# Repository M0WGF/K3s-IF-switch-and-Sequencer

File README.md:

# K3/s IF switch and Sequencer
Two port IF switch and three event sequencer for use with the Elecraft K3 and K3s transceivers. 

Switch between two external transverters directly from the Elecraft K3/s transceiver, the unit also comes with a three
port sequencer where the first event is for switching a relay and the last two events pull to ground.

The unit is based around an Arduino UNO see the .ino file for the script, it uses one no standard library which is
called Bounce2 and be downloaded from https://github.com/thomasfredericks/Bounce2

The unit has also been designed so that when the VSWR trip is pulled to ground the unit goes into a disabled state
stopping the transmitter and sounding a buzzer until the unit is reset. 

There are two boards the main board and an indicator board.  

The software has few parameters that can be changed look towards the top of the .ino file these are

// Event Sequence Delays 

int Sequence_Delay = 50; // Delay in milliseconds.
int Txinhibit_Delay = 50; 

// Default RX behaviour of events HIGH = On; LOW = Off.   Event 1 is capable of providing upto 28V 1A, and by default is 
set to energise the relay for RX.

int band0_event1 = HIGH;
int band0_event2 = LOW;
int band0_event3 = LOW;

int band1_event1 = HIGH;
int band1_event2 = LOW;
int band1_event3 = LOW;

// Debugging will output the debugs to the serial port. 
bool debug_main = false;

For further details see : 
https://m0wgf.blogspot.com/2019/12/dual-transverter-if-switch-and.html

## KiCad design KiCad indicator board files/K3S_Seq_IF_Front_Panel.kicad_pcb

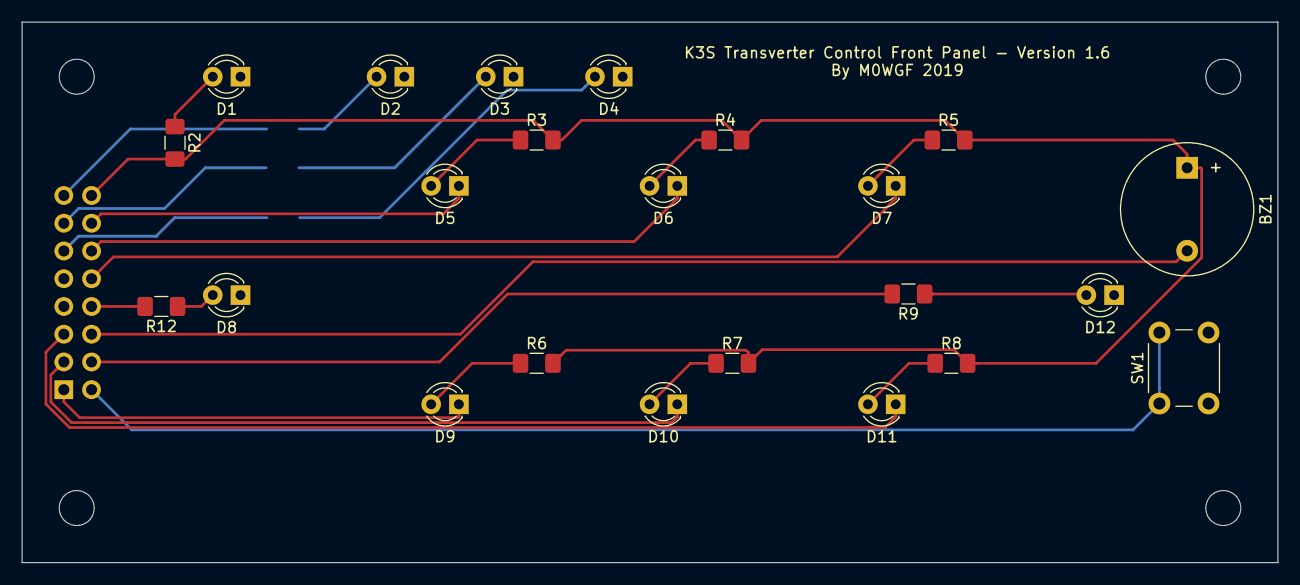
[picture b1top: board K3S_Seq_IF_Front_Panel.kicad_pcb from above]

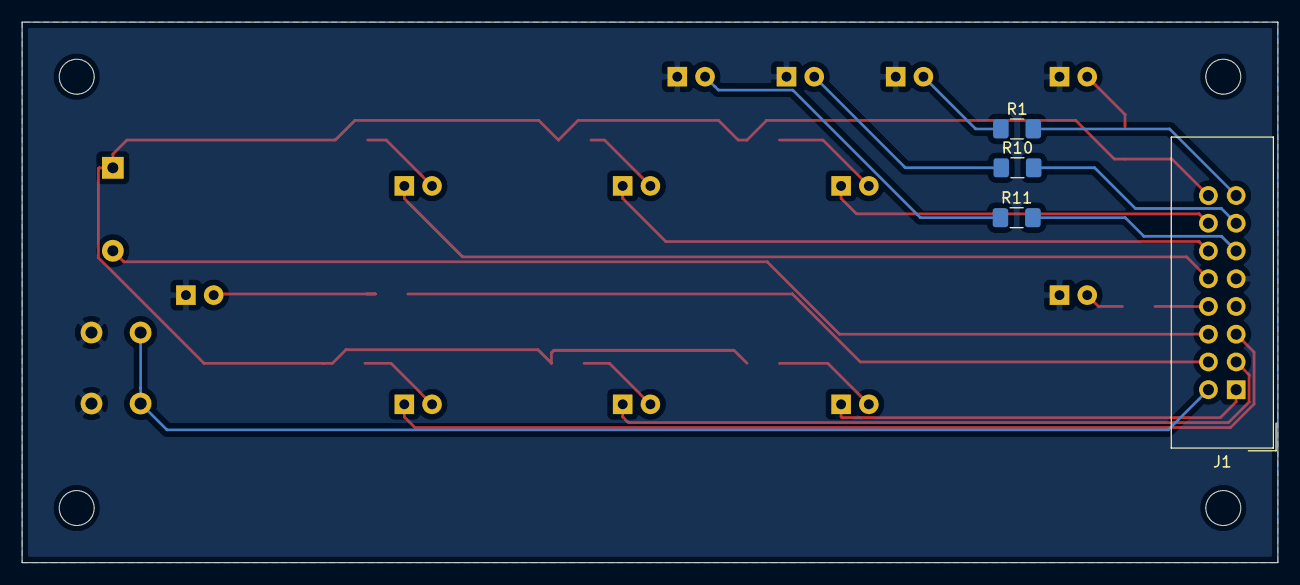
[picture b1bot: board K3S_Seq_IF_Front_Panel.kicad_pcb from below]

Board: 2 copper layers, 115.0 x 49.5 mm, 27 parts (4 on the bottom side), 27 nets.

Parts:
BZ1: VSWR Trip Buzzer; Buzzer_12x9.5RM7.6
D1: Power; LED_D3.0mm
D2: Band 0; LED_D3.0mm
D3: Band 1; LED_D3.0mm
D4: Band 2; LED_D3.0mm
D5: Band 0 Event 1; LED_D3.0mm
D6: Band 0 Event 2; LED_D3.0mm
D7: Band 0 Event 3; LED_D3.0mm
D8: PTT; LED_D3.0mm
D9: Band 1 Event 1; LED_D3.0mm
D10: Band 1 Event 2; LED_D3.0mm
D11: Band 1 Event 3; LED_D3.0mm
D12: Tx Inhibit; LED_D3.0mm
J1: Conn_02x08_Odd_Even; IDC-Header_2x08_P2.54mm_Vertical
R1, R2, R3, R4, R5, R6, R7, R8, R9, R10, R11, R12: 360; R_1206_3216Metric_Pad1.42x1.75mm_HandSolder
SW1: RESET SW; SW_PUSH_6mm

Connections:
+5V: BZ1.1, J1.16, R2.2, R3.2, R4.2, R5.2, R6.2, R7.2, R8.2
Band0_Event1_Led: D5.1, J1.14
Band0_Event2_Led: D6.1, J1.12
Band0_Event3_Led: D7.1, J1.10
Band0_Led: J1.15, R1.2
Band1_Event1_Led: D9.1, J1.1
Band1_Event2_Led: D10.1, J1.3
Band1_Event3_Led: D11.1, J1.5
Band1_Led: J1.13, R10.2
Band2_Led: J1.11, R11.2
Buzzer: BZ1.2, J1.6
GND: D1.1, D2.1, D3.1, D4.1, D8.1, D12.1, J1.9, SW1.2
unnamed: D1.2, R2.1
unnamed: D2.2, R1.1
unnamed: D3.2, R10.1
unnamed: D4.2, R11.1
unnamed: D5.2, R3.1
unnamed: D6.2, R4.1
unnamed: D7.2, R5.1
unnamed: D8.2, R12.1
unnamed: D9.2, R6.1
unnamed: D10.2, R7.1
unnamed: D11.2, R8.1
unnamed: D12.2, R9.1
PTT_Led: J1.8, R12.2
Reset: J1.2, SW1.1
TxInhibit_Led: J1.4, R9.2

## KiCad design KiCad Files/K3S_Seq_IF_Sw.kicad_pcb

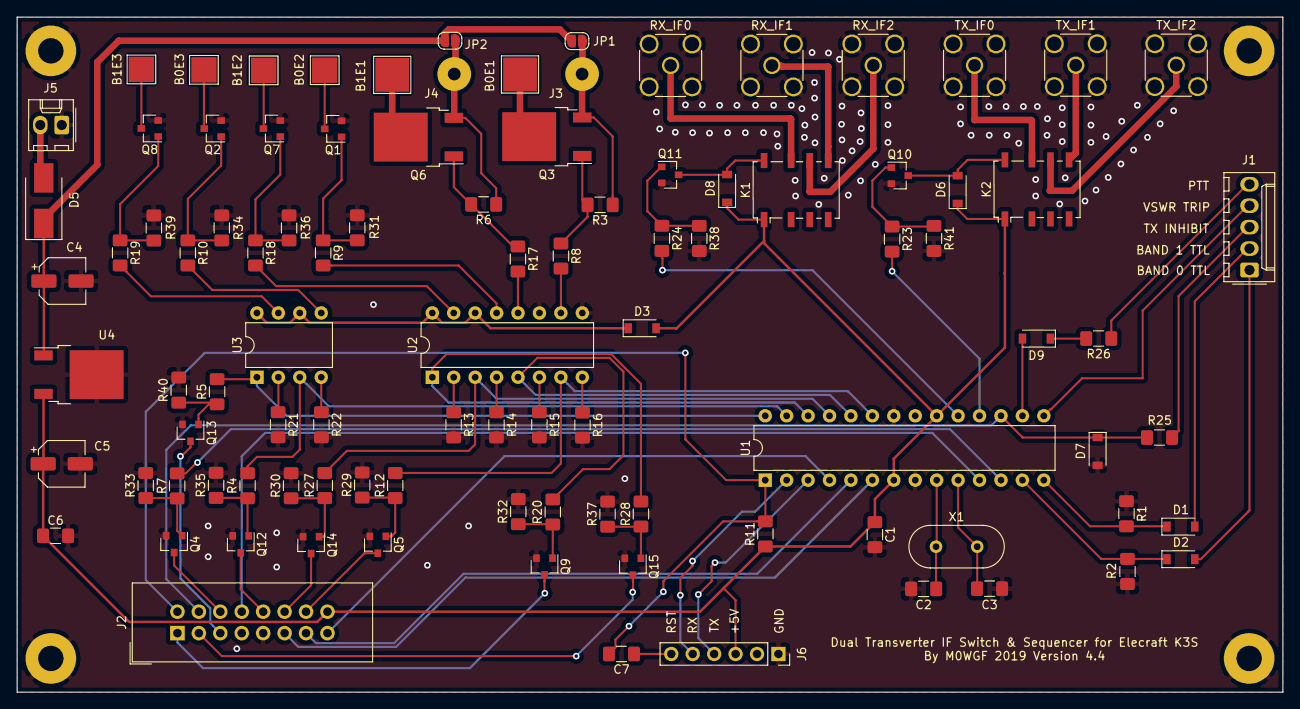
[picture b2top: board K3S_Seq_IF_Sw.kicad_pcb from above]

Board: 2 copper layers, 150.0 x 80.0 mm, 102 parts (0 on the bottom side), 84 nets.

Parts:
B0E1, B1E1: Conn_01x01; TestPoint_Pad_4.0x4.0mm
B0E2, B0E3, B1E2, B1E3: Conn_01x01; TestPoint_Pad_3.0x3.0mm
C1, C6, C7: 100nF; C_1206_3216Metric_Pad1.42x1.75mm_HandSolder
C2, C3: 22pF; C_1206_3216Metric_Pad1.42x1.75mm_HandSolder
C4, C5: 47uF; CP_Elec_5x5.8
D1, D2, D3, D6, D8, D9: D; D_SOD-123
D5: D; D_SMB_Handsoldering
D7: 5V1; D_SOD-123
H1, H2, H3, H4: MountingHole; MountingHole_3mm_Pad
J1: K3S & Wavenode; Molex_KK-254_AE-6410-05A_1x05_P2.54mm_Vertical
J2: Indicator Panel; IDC-Header_2x08_P2.54mm_Vertical
J3, J4: 12V; SolderWirePad_1x01_Drill1.5mm
J5: PWR; Molex_KK-254_AE-6410-02A_1x02_P2.54mm_Vertical
J6: Programming Interface; PinSocket_1x06_P2.54mm_Vertical
JP1, JP2: Jumper; SolderJumper-2_P1.3mm_Open_RoundedPad1.0x1.5mm
K1, K2: G6K-2; Relay_DPDT_Omron_G6K-2F-Y
Q1, Q2, Q4, Q5, Q7, Q8, Q9, Q10, Q11, Q12, Q13, Q14, Q15: MMBT3904; SOT-23
Q3, Q6: DMP4015SK3; TO-252-2
R1, R2, R3, R6, R11, R25, R26, R29, R30, R31, R32, R33, R34, R35, R36, R37, R38, R39, R40, R41: 10k; R_1206_3216Metric_Pad1.42x1.75mm_HandSolder
R4, R5, R7, R9, R10, R12, R18, R19, R20, R23, R24, R27, R28: 2k2; R_1206_3216Metric_Pad1.42x1.75mm_HandSolder
R8, R17: 100; R_1206_3216Metric_Pad1.42x1.75mm_HandSolder
R13, R14, R15, R16, R21, R22: 330; R_1206_3216Metric_Pad1.42x1.75mm_HandSolder
RX_IF0: RX_IF0; SMA_Amphenol_132134-16_Vertical
RX_IF1: RX_IF1; SMA_Amphenol_132134-16_Vertical
RX_IF2: RX_IF; SMA_Amphenol_132134-16_Vertical
TX_IF0: TX_IF0; SMA_Amphenol_132134-16_Vertical
TX_IF1: TX_IF1; SMA_Amphenol_132134-16_Vertical
TX_IF2: TX_IF; SMA_Amphenol_132134-16_Vertical
U1: ATmega328P-PU; DIP-28_W7.62mm
U2: LTV-847S; DIP-16_W7.62mm
U3: LTV-827S; DIP-8_W7.62mm
U4: MC7805BDTG; TO-252-2
X1: Crystal; Crystal_HC49-U_Vertical

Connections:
+5V: C1.1, C5.1, C6.1, D3.2, D6.1, D8.1, J2.16, J6.3, K1.1, K2.1, R11.1, U1.7, U1.20, U4.3
+12V: C4.1, D5.1, JP1.1, JP2.1, U4.1
Band0_Event1: R12.2, U1.23, U2.7
Band0_Event1_Led: J2.14, Q5.3
Band0_Event2: R27.2, U1.25, U2.3
Band0_Event2_Led: J2.12, Q14.3
Band0_Event3: R4.2, U1.27, U3.3
Band0_Event3_Led: J2.10, Q12.3
Band0_Input: D2.2, J1.1
Band0_Led: J2.15, U1.4
Band1_Event1: R20.2, U1.24, U2.5
Band1_Event1_Led: J2.1, Q9.3
Band1_Event2: R28.2, U1.26, U2.1
Band1_Event2_Led: J2.3, Q15.3
Band1_Event3: R5.2, U1.28, U3.1
Band1_Event3_Led: J2.5, Q13.3
Band1_Input: D1.2, J1.2
Band1_Led: J2.13, U1.5
Band2_Led: J2.11, U1.6
Buzzer: J2.6, Q4.3
D0: J6.5, U1.2
D1: J6.4, U1.3
GND: C1.2, C2.2, C3.2, C4.2, C5.2, C6.2, D7.2, H1.1, H2.1, H3.1, H4.1, J2.9, J5.1, J6.1, Q1.2, Q2.2, Q4.2, Q5.2, Q7.2, Q8.2, Q9.2, Q10.2, Q11.2, Q12.2, Q13.2, Q14.2, Q15.2, R1.1, R2.2, R13.2, R14.2, R15.2, R16.2, R21.2, R22.2, R29.2, R30.2, R31.2, R32.2, R33.2, R34.2, R35.2, R36.2, R37.2, R38.2, R39.2, R40.2, R41.2, RX_IF0.2, RX_IF1.2, RX_IF2.2, TX_IF0.2, TX_IF1.2, TX_IF2.2, U1.8, U1.22, U2.9, U2.11, U4.2
IF_RX: R24.2, U1.19
IF_TX: R23.2, U1.18
unnamed: B0E1.1, Q3.2
unnamed: B0E2.1, Q1.3
unnamed: B0E3.1, Q2.3
unnamed: B1E1.1, Q6.2
unnamed: B1E2.1, Q7.3
unnamed: B1E3.1, Q8.3
unnamed: C2.1, U1.9, X1.1
unnamed: C3.1, U1.10, X1.2
unnamed: C7.1, J6.6
unnamed: D1.1, R1.2, U1.14
unnamed: D2.1, R2.1, U1.13
unnamed: D5.2, J5.2
unnamed: D6.2, K2.8, Q10.3
unnamed: D8.2, K1.8, Q11.3
unnamed: D9.1, R26.2
unnamed: D9.2, U1.16
unnamed: J3.1, JP1.2, Q3.3, R3.1
unnamed: J4.1, JP2.2, Q6.3, R6.1
unnamed: K1.5, RX_IF1.1
unnamed: K1.6, RX_IF2.1
unnamed: K1.7, RX_IF0.1
unnamed: K2.5, TX_IF1.1
unnamed: K2.6, TX_IF2.1
unnamed: K2.7, TX_IF0.1
unnamed: Q1.1, R9.1, R31.1
unnamed: Q2.1, R10.1, R34.1
unnamed: Q3.1, R3.2, R8.1
unnamed: Q4.1, R7.1, R33.1
unnamed: Q5.1, R12.1, R29.1
unnamed: Q6.1, R6.2, R17.1
unnamed: Q7.1, R18.1, R36.1
unnamed: Q8.1, R19.1, R39.1
unnamed: Q9.1, R20.1, R32.1
unnamed: Q10.1, R23.1, R41.1
unnamed: Q11.1, R24.1, R38.1
unnamed: Q12.1, R4.1, R35.1
unnamed: Q13.1, R5.1, R40.1
unnamed: Q14.1, R27.1, R30.1
unnamed: Q15.1, R28.1, R37.1
unnamed: R7.2, U1.12
unnamed: R13.1, U2.2
unnamed: R14.1, U2.4
unnamed: R15.1, U2.6
unnamed: R16.1, U2.8
unnamed: R21.1, U3.2
unnamed: R22.1, U3.4
OptoA: R8.2, U2.10
OptoB: R17.2, U2.12
OptoC: R9.2, U2.13
OptoD: R18.2, U2.15
OptoE: R10.2, U3.5
OptoF: R19.2, U3.7
PTT_Input: J1.5, R26.1
PTT_Led: J2.8, U1.11
Reset: C7.2, J2.2, R11.2, U1.1
TX_Inhibit: J1.3, R25.1
TX_Inhibit_Drive: D7.1, J2.4, R25.2, U1.17
VSWR_Input: J1.4, U1.15
a: D3.1, U2.14, U2.16, U3.6, U3.8

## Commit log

2020-03-28 Added KiCad files and Gerber files.
2020-03-28 Updated readme title.
2020-03-28 Updated readme.
2020-03-28 Renamed the initial folder names so we can add the front display board stuff in awhile.
2020-03-28 First commit of the Arduino script.
2020-03-28 First commit of the indicator board and gerbers
2020-03-28 Updated the readme again.
2020-03-28 Added CVRS QUA article which is almost a mirror of the article on my website.
